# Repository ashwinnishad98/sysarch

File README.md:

# Non-invasive Sleep Analysis Device

## Description
This device aims to provide a non-invasive way of tracking an individual's sleep quality. It will leverage a force sensor that is placed underneath a mattress to quantify time spent in Rapid Eye Movement (REM) and Non-Rapid Eye Movement (Non-REM) sleep. The user will be able to see their sleep quality once awake, through a stepper-motor controlled gauge needle that indicated sleep quality percentage, which ranges from 0-100%.

## Power Consumption Spreadsheet
[URL](https://docs.google.com/spreadsheets/d/1Ds0gf-FW2-m5mJB0DvBmWuOtr-a-fM6qRe99MvLTX7Y/edit#gid=1000455818)

# Processor
## Seeed Xiao ESP32 S3
This microcontroller has both Wi-Fi and bluetooth capabilties, combined with a small form factor which is ideal for this device. It has 2 pins that can be used for supplying voltage, either 5V or 3.3V.

# Sensor
## Force Sensor: Bolsen Tech FSR402
This is a force sensor, that essentially converts pressure applied against the sensor into changes in resistance. This can be placed underneath the mattress to identify and track body movement over the sleep tracking period. It can be used within a range of 10KG-100KG.

# Displays

## Button
The button will be used by the user to start/stop the sleep tracking. Additionally, it will be programmed to where a double click shows if the device is currently tracking sleep through the LED output.

## LED
The LED will be used to indicate whether the device is currently tracking sleep and will be activated by the button. Upon double clicking the button, red will indicate that the device is not tracking and green will indicate vice-versa.

## Stepper-motor Needle Gauge
The needle gauge will display the measure of sleep quality in percentage. This output is triggered when the user clicks the button to stop the sleep tracking.

## System Architecture Diagram

## Functionality Diagram

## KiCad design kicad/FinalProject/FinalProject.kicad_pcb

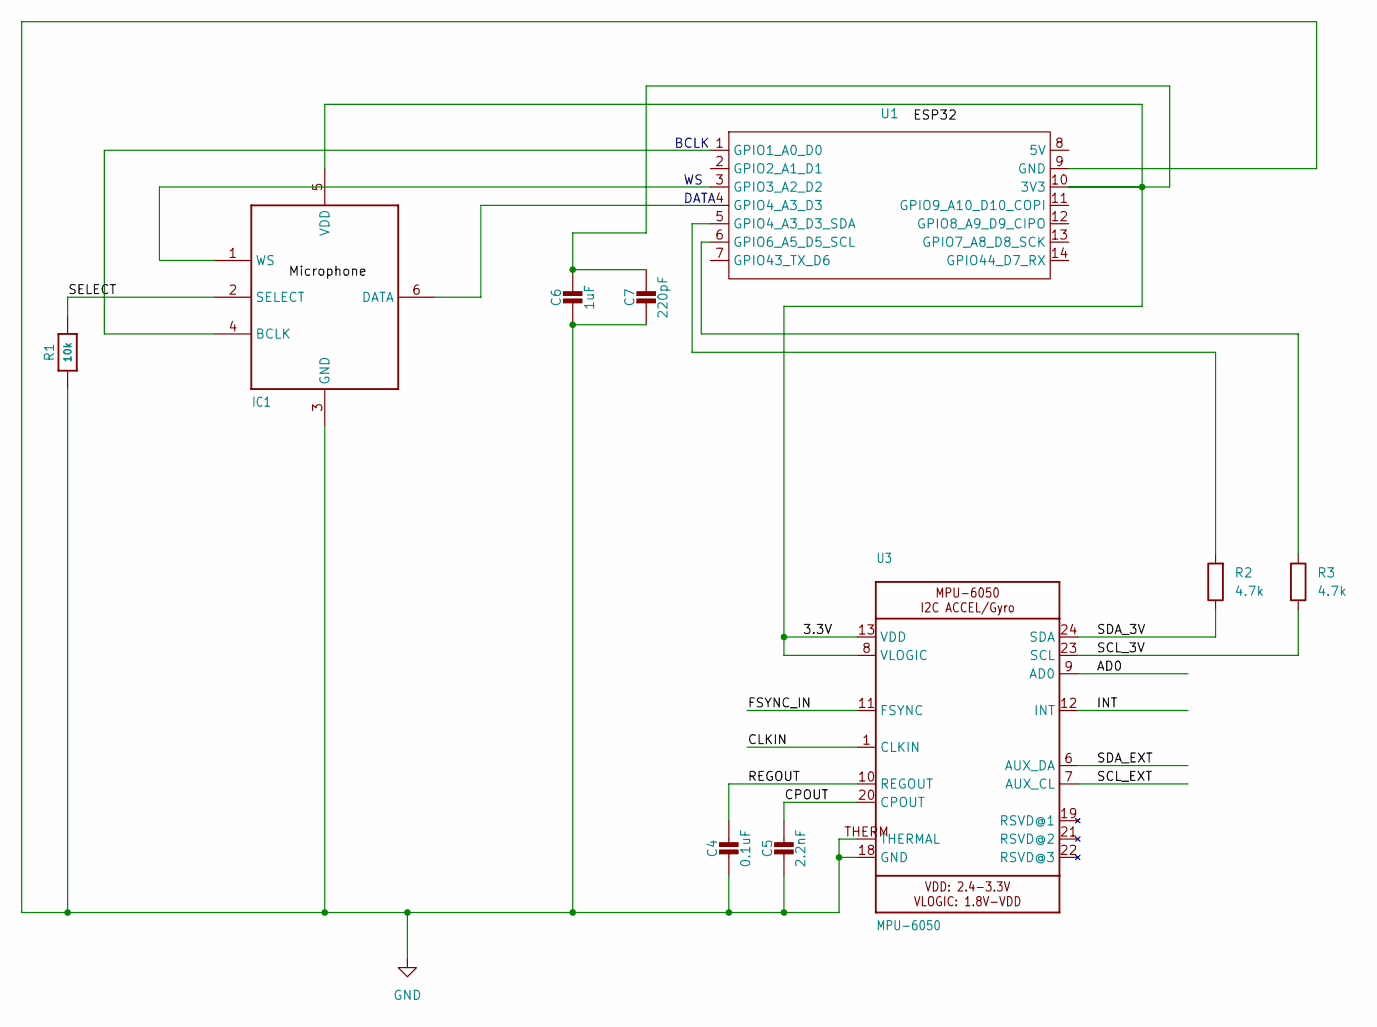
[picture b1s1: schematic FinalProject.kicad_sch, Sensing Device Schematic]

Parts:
C4: 0.1uF; 0603-NO
C5: 2.2nF; 0603-NO
C6: 1uF; 0805-NO
C7: 220pF; 0805-NO
IC1: MIC_I2S_SPH0645; SPH0645LM4H
R1: 10k; 0603-NO
R2, R3: 4.7k; 0603-NO
U1: XIAO_ESP32_SENSE
U3: MPU-6050; QFN24_4MM_SMSC

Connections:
/3.3V: C6.1, C7.1, IC1.5 (VDD), U1.10 (3V3), U3.8 (VLOGIC), U3.13 (VDD)
/AD0: U3.9 (AD0)
/CLKIN: U3.1 (CLKIN)
/CPOUT: C5.1, U3.20 (CPOUT)
/FSYNC_IN: U3.11 (FSYNC)
/INT: U3.12 (INT)
/REGOUT: C4.1, U3.10 (REGOUT)
/SCL_3V: R3.2, U3.23 (SCL)
/SCL_EXT: U3.7 (AUX_CL)
/SDA_3V: R2.1, U3.24 (SDA)
/SDA_EXT: U3.6 (AUX_DA)
/SELECT: IC1.2 (SELECT), R1.2
GND: C4.2, C5.2, C6.2, C7.2, IC1.3 (GND), R1.1, U1.9 (GND), U3.18 (GND), U3.THERM (THERMAL)
unnamed: IC1.4 (BCLK), U1.1 (GPIO1_A0_D0)
unnamed: IC1.6 (DATA), U1.4 (GPIO4_A3_D3)
unnamed: IC1.1 (WS), U1.3 (GPIO3_A2_D2)
unnamed: R2.2, U1.5 (GPIO4_A3_D3_SDA)
unnamed: R3.1, U1.6 (GPIO6_A5_D5_SCL)

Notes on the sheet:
DATA
BCLK

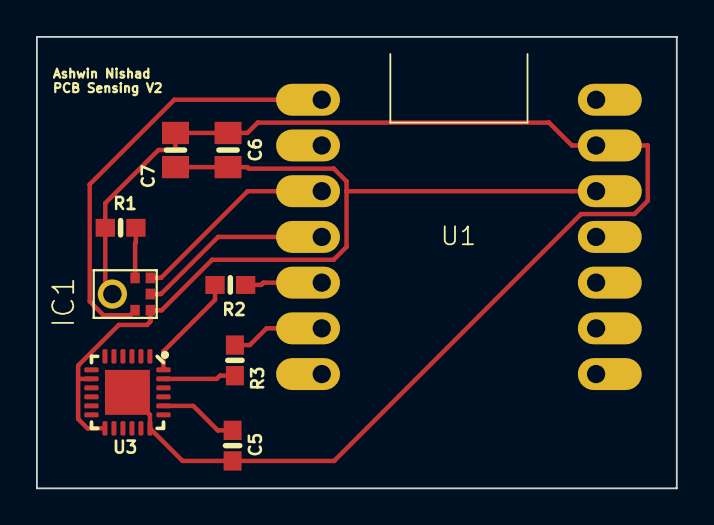
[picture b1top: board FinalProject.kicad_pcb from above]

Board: 2 copper layers, 35.5 x 25.1 mm, 9 parts (0 on the bottom side), 11 nets.

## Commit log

2024-01-16 initial
2024-01-17 added datasheets, updated readme, added images dir
2024-01-18 added initial v1 kicad schematic
2024-01-25 kicad/finalproject/ contains the kicad files for schematic and pcb
2024-02-06 added datasheets for led and stepper motor
2024-02-21 code for display device
2024-03-06 code for display and sensing
